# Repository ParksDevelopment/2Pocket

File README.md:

# 2Pocket

[Introduction](#Introduction)

[Info and Production](#Production)

[PCB](#PCB)

[Firmware](#Firmware)

[Case](#Case)

[Overview](#Overview)

## Introduciton

The 2Pocket is a pocket keyboard originally created for the [Pocket Keyboard Design Contest](https://chrischrislolo.github.io/orthoLabLogs/pocket-keyboard-design-contest-00.html). As such it was designed to meet the criteria of the contest as closely as possible while still being a practical keyboard for daily use. The feature list of the 2Pocket is pretty fleshed out including:

- 36 Kailh Choc V1 Low Profile Hot swap sockets (Using [Sunset](https://lowprokb.ca/collections/switches/products/sunset-tactile-choc-switches) switches for all pictures)
- Bluetooth support between halves and computer
- Pedometer using a ADXL345 for step counting
- 2 additional 6 mm Push button switches used for bluetooth, step reporting, or any othe KMK key
- Full open source customizeable keymap in KMK. ZMK to be included soon
- 2 3.7V 1100 mAh batteries Charged through the USB C port on the back of each board
- Magnetic casing to make the board unibody for preference, saving space, or travel
- Small enough to fit in your pocket! (according to the contest which gives a 190mm x 76mm x 22mm bounding box with the 2Pocket coming in comfortably at 190mm x 74.8mm x 22mm)

The idea behind the board was to create something that you can put in your pocket, ie fitting the bounding box, but does not force you to make any compromises to your work flow. I work a full time job as an software engineer and use a 36 key layout called [Miryoku](https://github.com/manna-harbour/miryoku_kmk) so it was important to me above all else to fit that standard so 36 keys was a must for me. I am able to hit 85 words per minute on it in monkey type 60 tests which is slower than my peak on a normal keyboard of 100 but definetly far from unpractical. Another key requirement for me was bluetooth. If this would be a pocket board then I would need it to be easier to bring places than my normal keyboard. The size helps but keeping it wireless allows me to pick it up on the way out the door or throw it in my bag without any fear of not having the necessary parts to make it run. Finally I wanted to play into the pocket part of the challenge which lead to the on board ADXL345. If I plan on keeping the board in my pocket It is already in the prime position to track my steps, and by mapping a button press to output my number of steps on the screen I am able to quickly see where I am at on the given day or trip. It gives me a great reason to still carry the board around even if I am not sure it will come in handy. Its not as accurate as a smart watch or even a smartphone but it gets pretty close and I am continuing to improve the step counting algorithem and features.

## Production

I will briefly explain below how to reproduce the board as well as discuss improvements that could be made in the future on the project in each area so. The production of the board is reletively simple, but will require either a 3D printer or ordering the case parts through a provider. I also chose to solder some parts and order the board with other parts soldered on. If you have a soldering station I would recommend you do the same but you can choose whatever works best for you. Below is the parts list which does not inclued the pcb or the case which will be discussed later:

| Part Name  | Quantity   | Solder by hand   |
|------------|------------|------------|
| Ceramic Capacitors 1uF| 4| NO|
| Tantalum Capacitors 10uF| 2| NO|
| ADXL345 | 2| NO|
| 1N4148 Diode | 38| NO|
| 4.7 k oHm Resistor | 4| NO|
| 2 pin Jst socket | 2| YES|
| 6 mm push button switches | 2| YES|
| Choc hotswap sockets | 36| YES|
| Xiao NRF52840 | 2| YES|
| EEMB Lithium Polymer Battery 3.7V 1100mAh | 2| DNA|

most of these the brand doesn't matter but the case is modeled to fit this specific battery so if you would like to use a different battery you need to make some modifications.

## PCB

The PCB has a footprint of 185mm x 71mm x 1.6mm which does not give a ton of room for the case but it is hard to scale it down much without giving up keys or making the wiring much more complicated. To order the case go to the PCB folder in this repo and then go to the production folder in there. that includes the gerber files as well as the BOM and POS files needed to order from jlcpbc. The original kicad project is there as well so if you need to regenerate the files that should be possible. the BOM will only inclued the parts I list as not soldered by hand. in addition double check the position of the ADXL345s. they should always be oriented so pin one is on the side closer to the Xiao board. Once the board is ordered just snap it in the middle and trim off any parts left over on the side. Then solder the remaining part on. 

I am pretty happy with the pcb but there are 2 big changes I would make:

1. I would wire the ncf pins on the xiao to the interupt pins on the adxl345. The ncf pins can act as extra gpio pins with some software changes and connecting them to the adxl345 would let me do things like shake to undo or stop any keystrokes if it detects the board has been knocked off. this stuff could still be done as is but I would need to check often and it would hurt the battery.
2. I could include a coulple mounting holes. I got by ok without them but some holes that are purely for helping connect it to the case would open up how you can design the case quite a bit.

## Firmware

The firmware is written in KMK. To install it just follow the [getting started](https://kmkfw.io/Getting_Started/) guide on the KMK site. After getting circuit python and kmk installed you should then follow the [bluetooth guide](https://kmkfw.io/ble_hid/) just up to adding the adafruit bluetooth folder into your project. Once that is done you can go to this repo, go to firmware, go to kmk and replace your code.py with the one there then take the adxl345.py and drag it into the extensions folder. Currently the keymap is Miryoku modified which used colemak DH mod. Once all that is done you can edit the keymap to your liking using KC.STEPS to print out how many steps have been taken and KC.CLEARBT to disconnect and pair to a new bluetooth device. kmk bluetooth can be finicky so if you run into issues you can ask at the [zmk help forum](https://kmkfw.zulipchat.com/#recent).

There is a lot I would touch on with the firmware, like I want to flesh out the step counter to keep the number in memory between shutting off so you don't lose it if the battery dies but the number one thing I will add is zmk support. I tried to have this done for the entry date for the contest and am very close but am having trouble getting the adxl345 to interface with zmk. once that is done I will add the zmk firmware here. zmk handles bluetooth much better than kmk so that alone would be worth it. 

## Case

The case is printed in 4 parts and requires a couple parts after the fact. It is pretty bare bones without a lot of bells and whistles due to only having about 5 mm to work with at most. That said it is sturdy enough to go in your pocket and has no gaps save for the usbc port to prevent dust or other things from getting into the board from your pocket. The parts needed are in the table below. I am linking to the ones I used but anything with these dimensions will work. or you can edit the case to fit something else. (I have no idea how affiliated links work but nothing I link to in this page has any affiliation with me and I don't benifit from)

| Part Name  | Quantity   | Link  |
|------------|------------|------------|
| Magnets | 8| [Link](https://www.amazon.com/dp/B0936M3WPK?ref=ppx_yo2ov_dt_b_fed_asin_title)|
| M3 threaded inserts| 4| [Link](https://www.amazon.com/dp/B0BQJ6CRNJ?ref=ppx_yo2ov_dt_b_fed_asin_title)|
| M3 flat head screws. shorter the better | 4| [Link](https://www.amazon.com/HanTof-Countersunk-Machine-Wrenches-Threaded/dp/B0B9HWVV61/ref=sr_1_3?crid=2YE6H5SPZ5472&dib=eyJ2IjoiMSJ9.L2XP8pYbu5l1a4j1_K4p1_b5aZn_wUVLVydeFWkYvYM0KNiWoAemW5YQWALzPugx6cIyMimG2n-ODHc8xE6avKn96-haNyTYAsjHn3l2HFDyPZpTqDHT6j0PfscB7inJyVgQs3MDA0USRKy3BG1DaQ6cNOfekXD1PnHhHwgLRrc8n5RaUJIK_YabDUsdGXFrJoy9bHcjiw26ildZeYGJ4g01n6a7OgG01xCU7sdOgdtkfw9zkb8ot_BvuKhA_g9635XTGlkiBysZ89JSAjQQBHvJiuZJ-d6szBEDqgJjcdw.fwF4DNqeGYTvOX1p3F9zsEH2r3VcWQ9_gU5F2RgjjSw&dib_tag=se&keywords=M3%2Bflat%2Bhead%2Bscrews&qid=1725912902&s=industrial&sprefix=m3%2Bflat%2Bhead%2Bscrews%2Cindustrial%2C177&sr=1-3&th=1)|

The top of the case has 2 small holes on the side that is flat and would touch the other half of the keyboard. In both those holes insert the magnets so they are flush and then glue the backs of them around the hole on the inside of the case. Repeat of the other half and let sit.

The bottom half has One set of holes near the battery holder and one set on the other side of the case. The set on the side with the battery holder will hold the magnets. Put some glue at the back and then insert them. The other set of holes need the threaded inserts inside. I use a soldering iron with a M3 tip but you can use any method you would like. 

To combine everything put some keys in the top, push the pcb into the case so the keys go into the hot swap sockets. Then take the bottom, put the battery in the holder and connect it to the jst connector. Then put the bottom on, the magnets should line it all up. Finally screen in the m3 screws on the other side untill they are flush.

The case could be improved in a lot of areas. I have very limited experience with 3D modeling so I have no doubt it can be done much better. I would probably redesign it once I have mounting holes to screw in from the bottom so I don't have to sacrifice the sides so much just to allow for a connection. This is the first part I would do a complete overhaul on but for now it works well enough, keeping the board and battery secure while staying within the bounding box, barely.

## Overview

Overall I am very happy with the board and think it fit the criteria of the contest while being a practical board for me to use. The extra gimmick of acting as a pedometer only adds to the charm and my enjoyment of bringing it out of the house. I am excited to keep interating on it in the future but know the board as it stands is fully functional and will be used as my daily driver for a couple days to prove that. I also want to thank Chris Lo aka sporewoh for putting on the contest. It was very fun to design the project fitting into a certain critera and being pushed to add gimmicks and functionality into such small size.

If you enjoyed or found and of the information helpful consider [Buying me a coffee](https://buymeacoffee.com/parks) to keep working on projects like this!

p.s. enjoy the [extra photos](https://photos.app.goo.gl/FVwNr18BBK3Yw1VW6) my wife took of the board on a hike

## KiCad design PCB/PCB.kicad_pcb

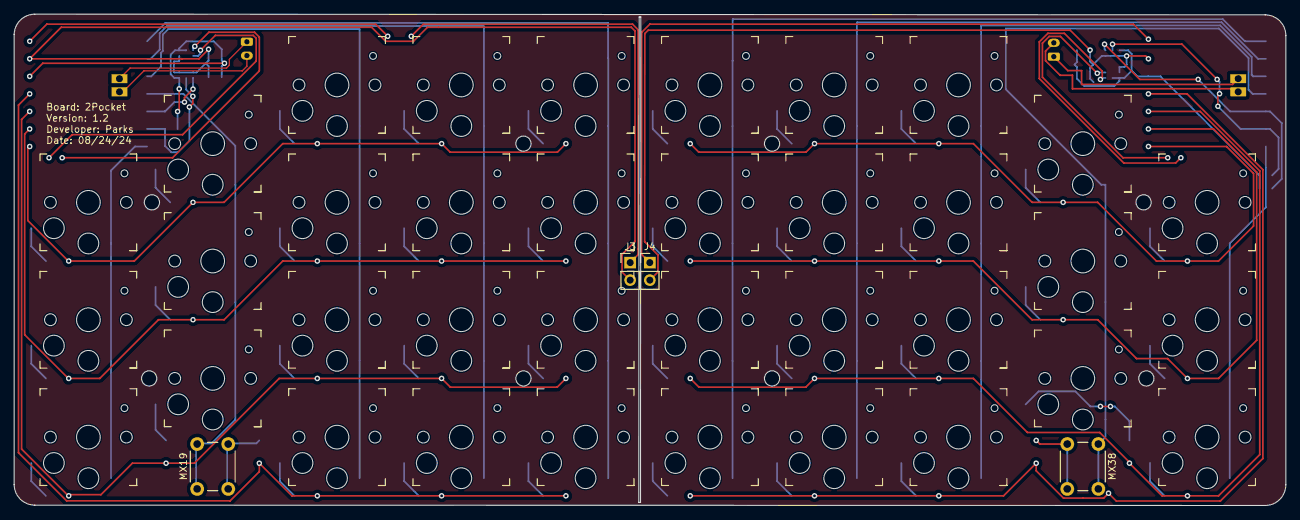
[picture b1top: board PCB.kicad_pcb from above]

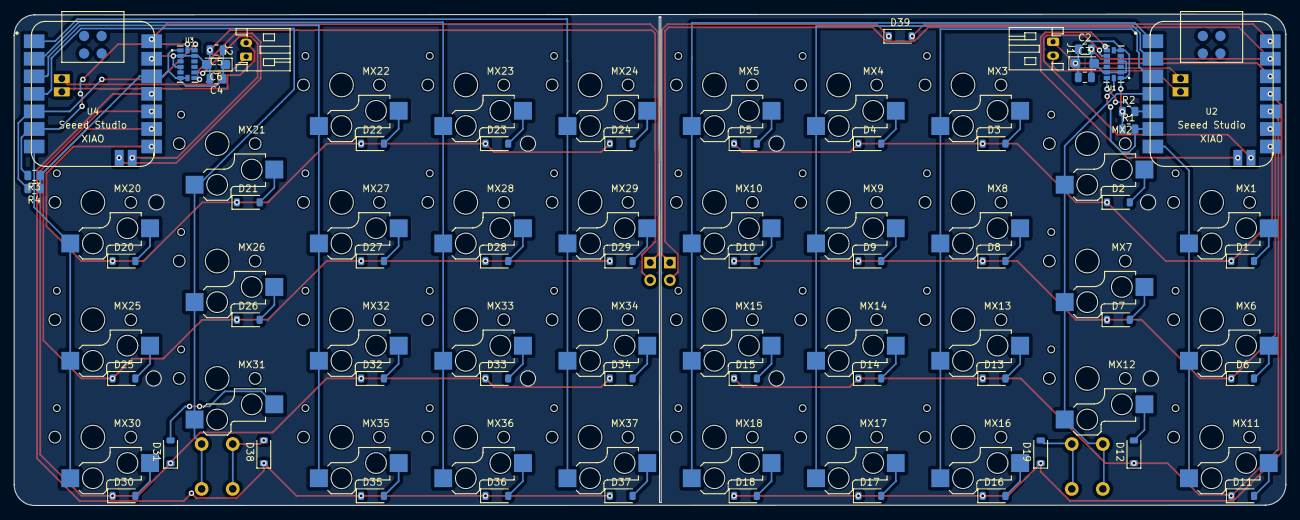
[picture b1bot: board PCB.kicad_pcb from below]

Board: 2 copper layers, 184.2 x 71.2 mm, 95 parts (55 on the bottom side), 75 nets.

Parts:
C1, C2, C4, C5: C; C_0805_2012Metric
C3, C6: C_Polarized_US; CP_EIA-3216-18_Kemet-A
D1, D2, D3, D4, D5, D6, D7, D8, D9, D10, D11, D12, D13, D14, D15, D16, D17, D18, D19, D20, D21, D22, D23, D24, D25, D26, D27, D28, D29, D30, D31, D32, D33, D34, D35, D36, D37, D38: D_Small; D_SOD-123
D39: D_Schottky; D_SOD-123
J1, J2: Conn_01x02; JST_PH_S2B-PH-K_1x02_P2.00mm_Horizontal
J3, J4: Conn_01x02; PinHeader_1x02_P2.54mm_Vertical
MX1, MX2, MX3, MX4, MX5, MX6, MX7, MX8, MX9, MX10, MX11, MX12, MX13, MX14, MX15, MX16, MX17, MX18, MX20, MX21, MX22, MX23, MX24, MX25, MX26, MX27, MX28, MX29, MX30, MX31, MX32, MX33, MX34, MX35, MX36, MX37: MX-NoLED; Kailh_socket_PG1350
MX19, MX38: MX-NoLED; SW_PUSH_6mm
R1, R2, R3, R4: R; R_0805_2012Metric
U1, U3: ADXL345; PQFN80P500X300X100-14N
U2, U4: Seeed Studio XIAO nRF52840; XIAO-nRF52840-Sense-14P-2.54-21X17.8MM

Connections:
+3.3V: C1.1, C2.1, C3.1, R1.1, R2.1, U1.1 (VDD_I/O), U1.6 (VS), U1.7 (~CS), U2.12 (3V3)
+3.3VA: C4.1, C5.1, C6.1, R3.1, R4.1, U3.1 (VDD_I/O), U3.6 (VS), U3.7 (~CS), U4.12 (3V3)
+5V: D39.2 (A), U2.14 (5V)
+5VA: J4.1, U4.14 (5V)
/Bat+: J1.2, U2.22 (BAT+)
/Bat+B: J2.2, U4.22 (BAT+)
/Bat-: J1.1, U2.21 (BAT-)
/Bat-B: J2.1, U4.21 (BAT-)
/Col0: MX1.1 (COL), MX6.1 (COL), MX11.1 (COL), U2.7 (P1.11_D6_TX)
/Col0B: MX20.1 (COL), MX25.1 (COL), MX30.1 (COL), U4.7 (P1.11_D6_TX)
/Col1: MX2.1 (COL), MX7.1 (COL), MX12.1 (COL), MX19.1 (COL), U2.4 (P0.29_A3_D3)
/Col1B: MX21.1 (COL), MX26.1 (COL), MX31.1 (COL), MX38.1 (COL), U4.4 (P0.29_A3_D3)
/Col2: MX3.1 (COL), MX8.1 (COL), MX13.1 (COL), MX16.1 (COL), U2.3 (P0.28_A2_D2)
/Col2B: MX22.1 (COL), MX27.1 (COL), MX32.1 (COL), MX35.1 (COL), U4.3 (P0.28_A2_D2)
/Col3: MX4.1 (COL), MX9.1 (COL), MX14.1 (COL), MX17.1 (COL), U2.2 (P0.03_A1_D1)
/Col3B: MX23.1 (COL), MX28.1 (COL), MX33.1 (COL), MX36.1 (COL), U4.2 (P0.03_A1_D1)
/Col4: MX5.1 (COL), MX10.1 (COL), MX15.1 (COL), MX18.1 (COL), U2.1 (P0.02_A0_D0)
/Col4B: MX24.1 (COL), MX29.1 (COL), MX34.1 (COL), MX37.1 (COL), U4.1 (P0.02_A0_D0)
/I1: U1.8 (INT1), U2.19 (P0.09_NFC1)
/I1B: U3.8 (INT1), U4.19 (P0.09_NFC1)
/I2: U1.9 (INT2), U2.20 (P0.10_NFC2)
/I2B: U3.9 (INT2), U4.20 (P0.10_NFC2)
/Row0: D1.1 (K), D2.1 (K), D3.1 (K), D4.1 (K), D5.1 (K), U2.8 (P1.12_D7_RX)
/Row0B: D20.1 (K), D21.1 (K), D22.1 (K), D23.1 (K), D24.1 (K), U4.8 (P1.12_D7_RX)
/Row1: D6.1 (K), D7.1 (K), D8.1 (K), D9.1 (K), D10.1 (K), U2.9 (P1.13_D8_SCK)
/Row1B: D25.1 (K), D26.1 (K), D27.1 (K), D28.1 (K), D29.1 (K), U4.9 (P1.13_D8_SCK)
/Row2: D11.1 (K), D12.1 (K), D13.1 (K), D14.1 (K), D15.1 (K), U2.10 (P1.14_D9_MISO)
/Row2B: D30.1 (K), D31.1 (K), D32.1 (K), D33.1 (K), D34.1 (K), U4.10 (P1.14_D9_MISO)
/Row3: D16.1 (K), D17.1 (K), D18.1 (K), D19.1 (K), U2.11 (P1.15_D10_MOSI)
/Row3B: D35.1 (K), D36.1 (K), D37.1 (K), D38.1 (K), U4.11 (P1.15_D10_MOSI)
/SCL: R1.2, U1.14 (SCL/SCLK), U2.6 (P0.05_A5_D5_SCL)
/SCLB: R3.2, U3.14 (SCL/SCLK), U4.6 (P0.05_A5_D5_SCL)
/SDA: R2.2, U1.13 (SDA/SDI/SDIO), U2.5 (P0.04_A4_D4_SDA)
/SDAB: R4.2, U3.13 (SDA/SDI/SDIO), U4.5 (P0.04_A4_D4_SDA)
GND: C1.2, C2.2, C3.2, J3.2, U1.2 (GND), U1.4 (GND), U1.5 (GND), U1.12 (SDO/ALT_ADDRESS), U2.13 (GND)
GND1: C4.2, C5.2, C6.2, J4.2, U3.2 (GND), U3.4 (GND), U3.5 (GND), U3.12 (SDO/ALT_ADDRESS), U4.13 (GND)
unnamed: D1.2 (A), MX1.2 (ROW)
unnamed: D2.2 (A), MX2.2 (ROW)
unnamed: D3.2 (A), MX3.2 (ROW)
unnamed: D4.2 (A), MX4.2 (ROW)
unnamed: D5.2 (A), MX5.2 (ROW)
unnamed: D6.2 (A), MX6.2 (ROW)
unnamed: D7.2 (A), MX7.2 (ROW)
unnamed: D8.2 (A), MX8.2 (ROW)
unnamed: D9.2 (A), MX9.2 (ROW)
unnamed: D10.2 (A), MX10.2 (ROW)
unnamed: D11.2 (A), MX11.2 (ROW)
unnamed: D12.2 (A), MX12.2 (ROW)
unnamed: D13.2 (A), MX13.2 (ROW)
unnamed: D14.2 (A), MX14.2 (ROW)
unnamed: D15.2 (A), MX15.2 (ROW)
unnamed: D16.2 (A), MX16.2 (ROW)
unnamed: D17.2 (A), MX17.2 (ROW)
unnamed: D18.2 (A), MX18.2 (ROW)
unnamed: D19.2 (A), MX19.2 (ROW)
unnamed: D20.2 (A), MX20.2 (ROW)
unnamed: D21.2 (A), MX21.2 (ROW)
unnamed: D22.2 (A), MX22.2 (ROW)
unnamed: D23.2 (A), MX23.2 (ROW)
unnamed: D24.2 (A), MX24.2 (ROW)
unnamed: D25.2 (A), MX25.2 (ROW)
unnamed: D26.2 (A), MX26.2 (ROW)
unnamed: D27.2 (A), MX27.2 (ROW)
unnamed: D28.2 (A), MX28.2 (ROW)
unnamed: D29.2 (A), MX29.2 (ROW)
unnamed: D30.2 (A), MX30.2 (ROW)
unnamed: D31.2 (A), MX31.2 (ROW)
unnamed: D32.2 (A), MX32.2 (ROW)
unnamed: D33.2 (A), MX33.2 (ROW)
unnamed: D34.2 (A), MX34.2 (ROW)
unnamed: D35.2 (A), MX35.2 (ROW)
unnamed: D36.2 (A), MX36.2 (ROW)
unnamed: D37.2 (A), MX37.2 (ROW)
unnamed: D38.2 (A), MX38.2 (ROW)
unnamed: D39.1 (K), J3.1

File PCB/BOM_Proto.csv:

"Id";"Designator";"Footprint";"Quantity";"Designation";"Supplier and ref";
1;"MX12,MX6,MX15,MX31,MX27,MX5,MX11,MX29,MX16,MX2,MX10,MX30,MX34,MX3,MX21,MX20,MX7,MX32,MX13,MX35,MX33,MX25,MX14,MX1,MX8,MX37,MX28,MX9,MX23,MX36,MX17,MX18,MX4,MX24,MX22,MX26";"Kailh_socket_PG1350";36;"MX-NoLED";;;
2;"MX19,MX38";"SW_PUSH_6mm";2;"MX-NoLED";;;
3;"D36,D8,D25,D27,D12,D1,D6,D9,D24,D38,D35,D20,D28,D19,D13,D23,D3,D17,D15,D34,D32,D18,D4,D21,D29,D16,D33,D30,D7,D37,D11,D2,D26,D22,D5,D10,D14,D31";"D_SOD-123";38;"D_Small";;;
4;"J2,J1";"JST_PH_S2B-PH-K_1x02_P2.00mm_Horizontal";2;"Conn_01x02";;;
5;"C6,C3";"CP_EIA-3216-18_Kemet-A";2;"C_Polarized_US";;;
6;"C5,C2,C4,C1";"C_0805_2012Metric";4;"C";;;
7;"U1,U3";"PQFN80P500X300X100-14N";2;"ADXL345";;;
8;"U2,U4";"XIAO-nRF52840-Sense-14P-2.54-21X17.8MM";2;"Seeed Studio XIAO nRF52840";;;
9;"R3,R2,R1,R4";"R_0805_2012Metric";4;"R";;;

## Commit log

2024-09-09 bulk
2024-09-10 Updating for submission
2024-09-10 Photo name updates
2024-11-11 1.2 changes for pass through charging and mounting
